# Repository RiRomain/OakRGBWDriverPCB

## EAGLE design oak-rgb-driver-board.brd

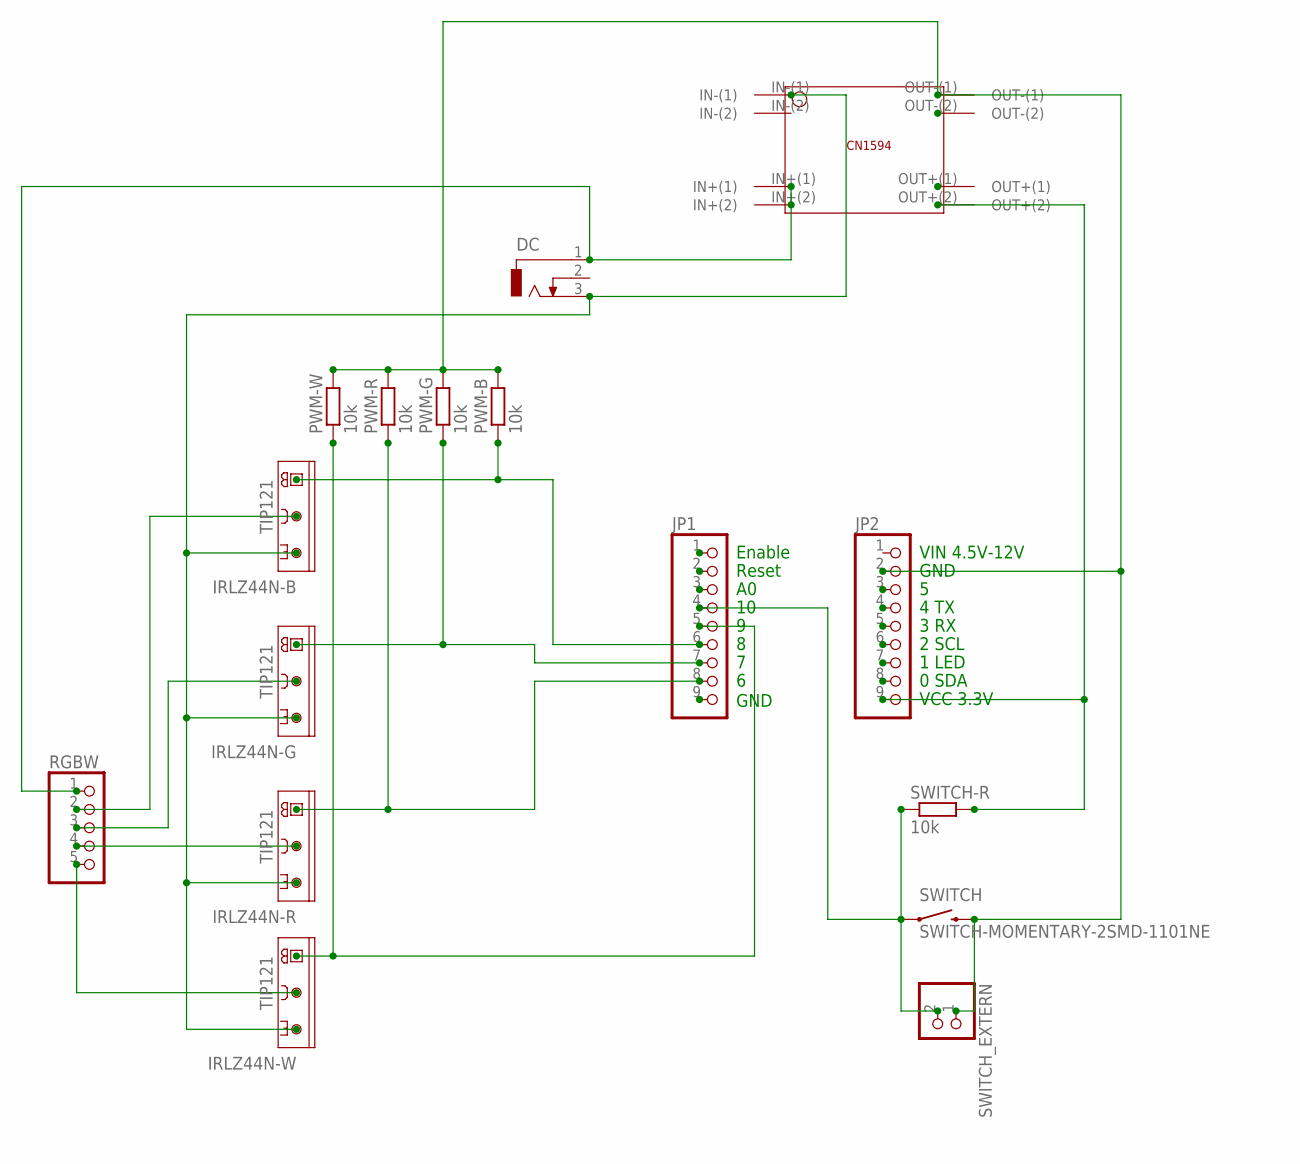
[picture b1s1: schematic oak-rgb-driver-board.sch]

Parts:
DC: DCJ0202
IRLZ44N-B, IRLZ44N-G, IRLZ44N-R, IRLZ44N-W: TIP121; TO220AV
JP1, JP2: PINHD-1X9; 1X09
PWM-B: 10k; R0603
PWM-G: 10k; R0603
PWM-R: 10k; R0603
PWM-W: 10k; R0603
RGBW: PINHD-1X5; 1X05
SWITCH: SWITCH-MOMENTARY-2SMD-1101NE; TACTILE-SWITCH-1101NE
SWITCH-R: 10k; R0603
SWITCH_EXTERN: PINHD-1X2; 1X02
U$1: CN1594THROUGH-HOLE; CN1594

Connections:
B_DRIVE: IRLZ44N-B.C, RGBW.2
GND: JP2.2, PWM-B.2, PWM-G.2, PWM-R.2, PWM-W.2, SWITCH.2, SWITCH_EXTERN.1, U$1.OUT-(1)
GND_IN: DC.3, IRLZ44N-B.E, IRLZ44N-G.E, IRLZ44N-R.E, IRLZ44N-W.E, U$1.IN-(1)
G_DRIVE: IRLZ44N-G.C, RGBW.3
P6_OUT: IRLZ44N-R.B, JP1.8, PWM-R.1
P7_OUT: IRLZ44N-G.B, JP1.7, PWM-G.1
P8_OUT: IRLZ44N-B.B, JP1.6, PWM-B.1
P9_OUT: IRLZ44N-W.B, JP1.5, PWM-W.1
P10_IN: JP1.4, SWITCH.1, SWITCH-R.1, SWITCH_EXTERN.2
R_DRIVE: IRLZ44N-R.C, RGBW.4
VCC_DC: DC.1, RGBW.1, U$1.IN+(1), U$1.IN+(2)
VCC_LOW: JP2.9, SWITCH-R.2, U$1.OUT+(2)
W_DRIVE: IRLZ44N-W.C, RGBW.5

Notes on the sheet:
Enable
Reset
GND
VIN 4.5V-12V
4 TX
3 RX
2 SCL
1 LED
0 SDA
VCC 3.3V

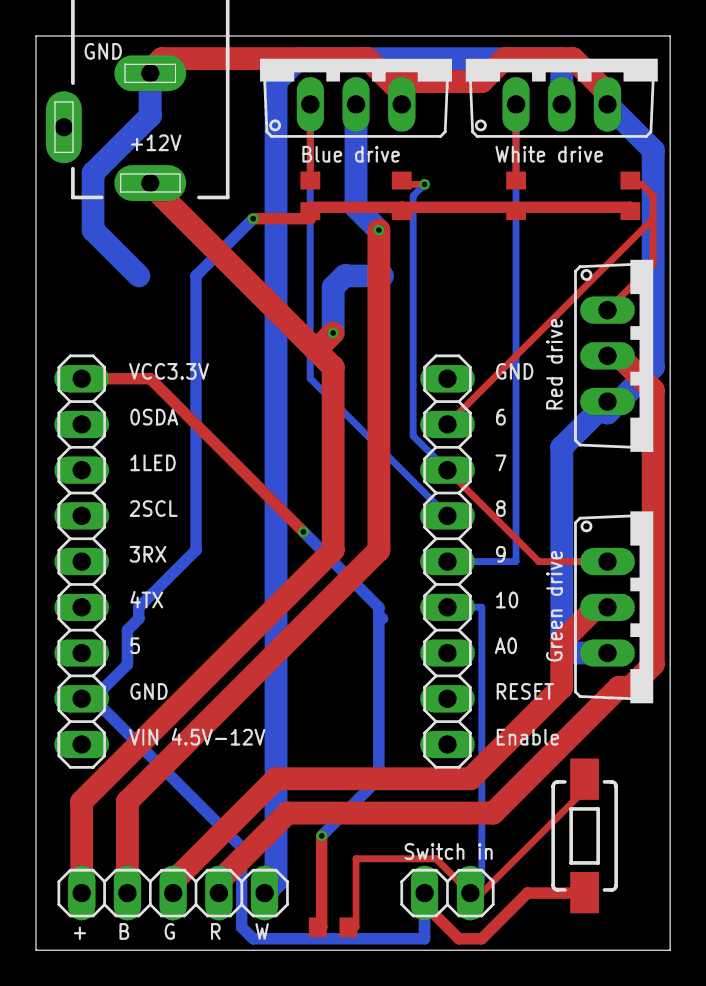
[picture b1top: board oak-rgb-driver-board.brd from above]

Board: 2 copper layers, 35.2 x 50.8 mm, 16 parts (1 on the bottom side), 13 nets.

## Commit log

2016-04-14 :tada: Added .gitattributes
2016-04-14 Commit of the PCB v0.1
    v0.1 with following function:
    -Integrated power converter
    -Push button to interact with the board through physical input (On/Off
    typically)
    -4 Channels to control an RGBW or an RGB + a White LED Strip
    -Support for the Digistump OAK Board

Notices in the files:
parts and their libraries:
SparkFun-Electromechanical: Licensing: Creative Commons ShareAlike 4.0 International - https://creativecommons.org/licenses/by-sa/4.0
